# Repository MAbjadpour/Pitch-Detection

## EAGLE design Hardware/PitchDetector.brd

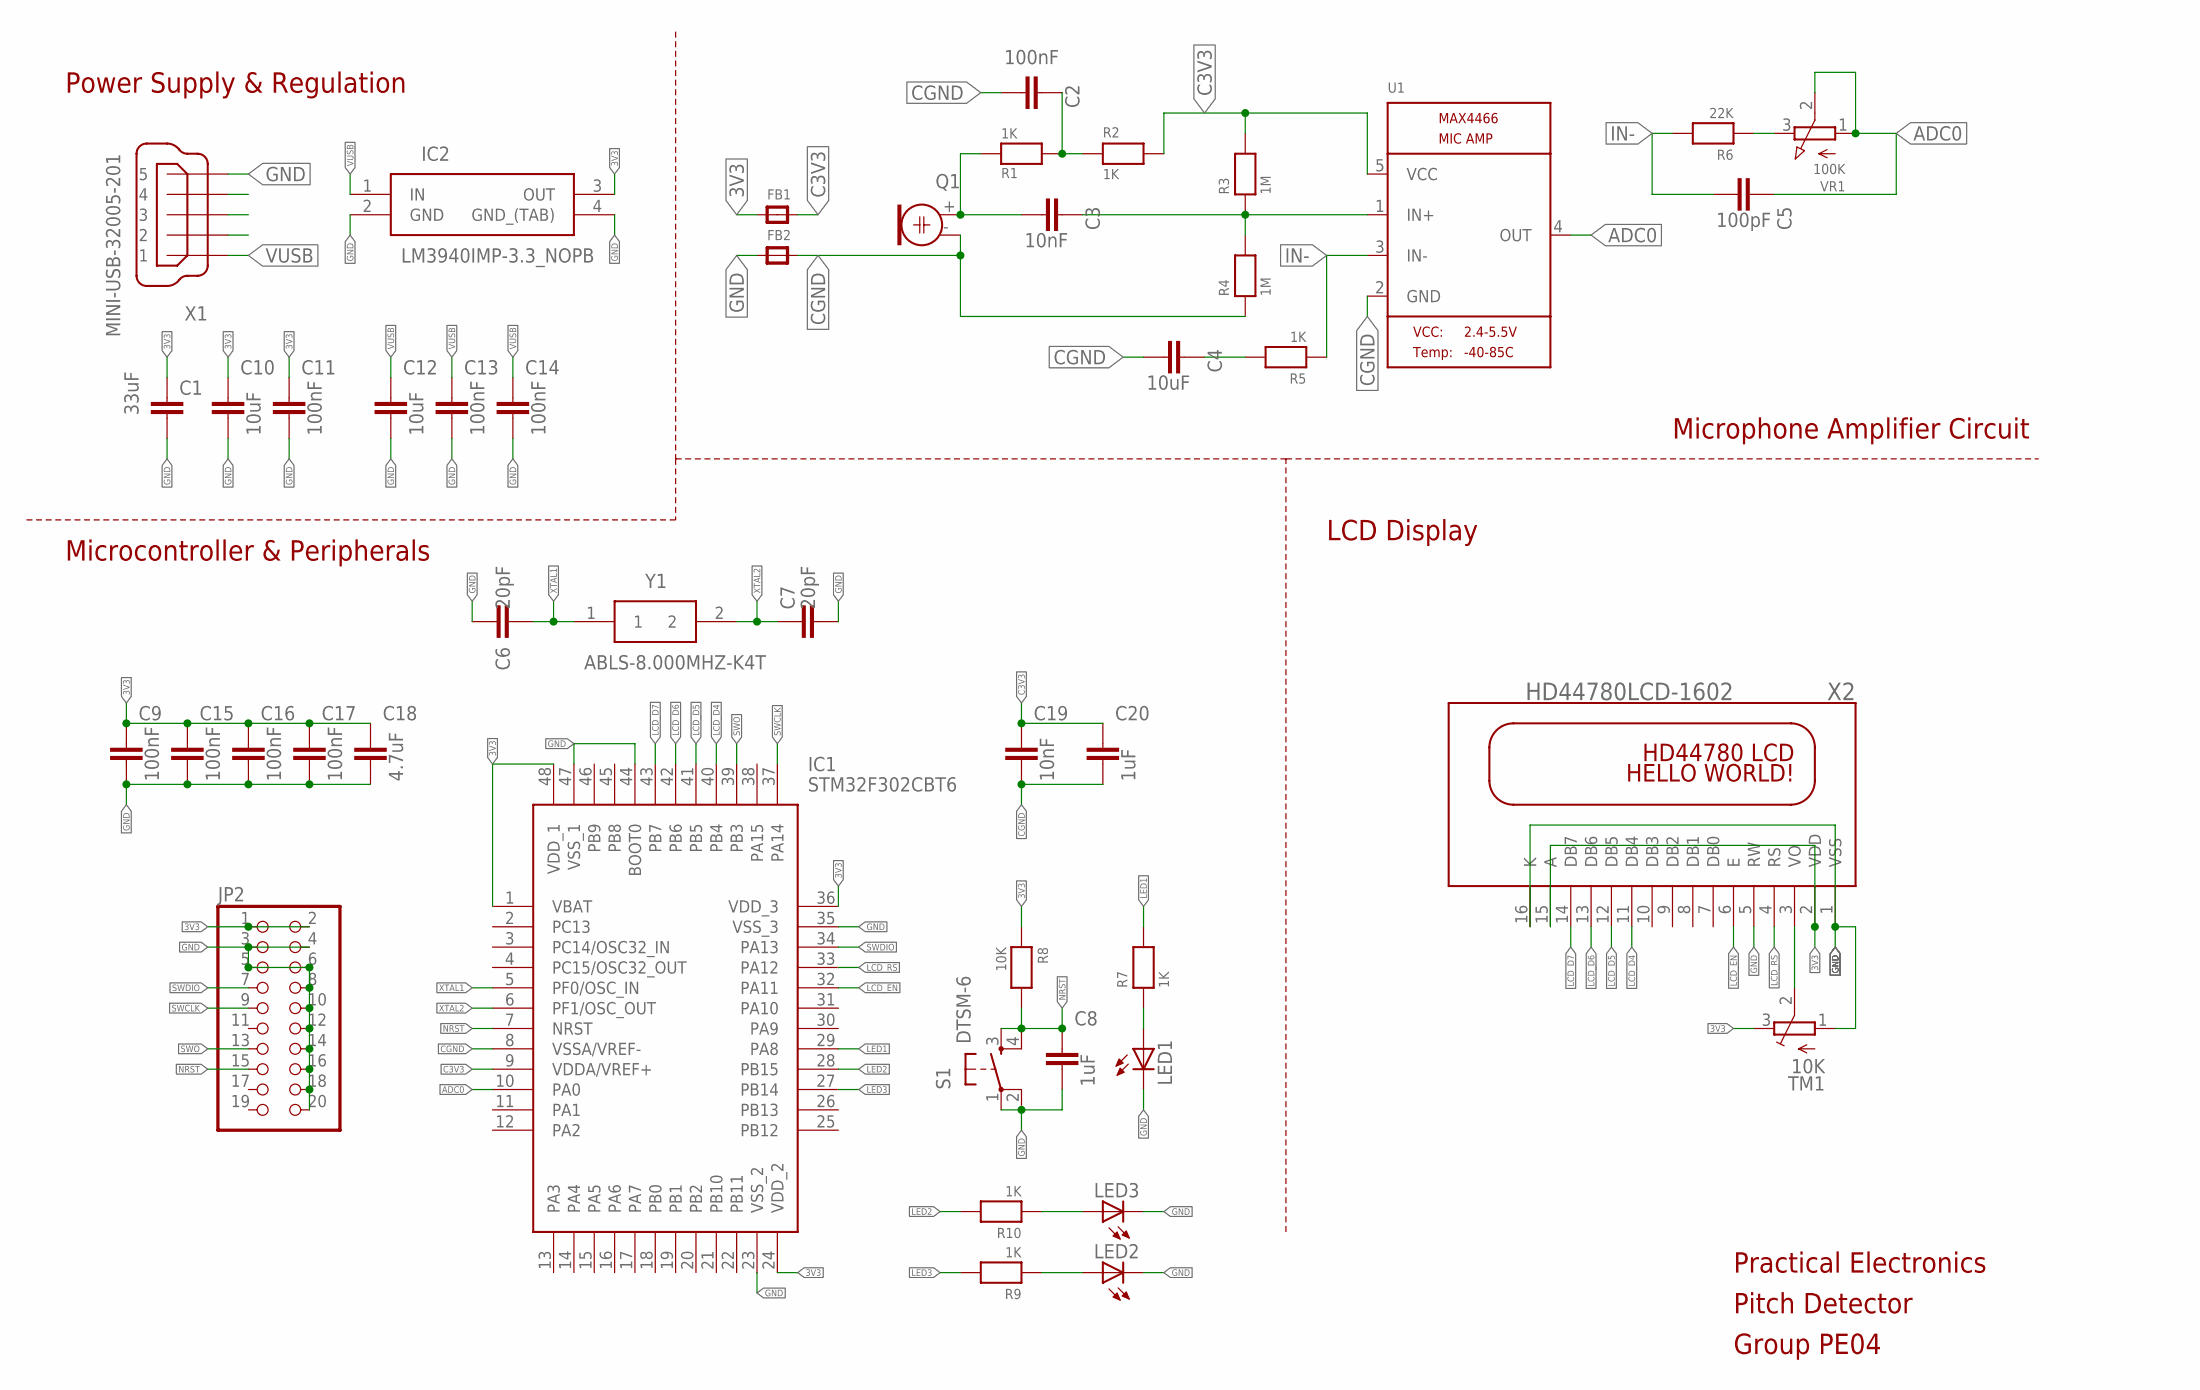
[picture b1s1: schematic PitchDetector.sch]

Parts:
C1: 33uF; C1206K
C2, C9, C11, C13, C14, C15, C16, C17: 100nF; C1206K
C3, C19: 10nF; C1206K
C4, C10, C12: 10uF; C1206K
C5: 100pF; C1206K
C6, C7: 20pF; C0805K
C8, C20: 1uF; C1206K
C18: 4.7uF; C1206K
FB1, FB2: MICROBUILDER_FERRITE_0805; MICROBUILDER__0805
IC1: STM32F302CBT6; QFP50P900X900X160-48N
IC2: LM3940IMP-3.3_NOPB; SOT230P700X180-4N
JP2: PINHD-2X10; 2X10
LED1, LED2, LED3: LEDCHIPLED_1206; CHIPLED_1206
Q1: MICROBUILDER_ELECTRET; MICROBUILDER_ELECTRET_9.7
R1, R2, R5, R7, R9, R10: 1K; MICROBUILDER_1206
R3, R4: 1M; MICROBUILDER_1206
R6: 22K; MICROBUILDER_1206
R8: 10K; MICROBUILDER_1206
S1: DTSM-6
TM1: 10K; TC33X
U1: MICROBUILDER_MAX4466""; MICROBUILDER_SC70-5
VR1: 100K; MICROBUILDER_TRIMPOT_BOURNS_TC33X-2
X1: MINI-USB-32005-201; 32005-201
X2: HD44780LCD-1602; LCD1602
Y1: ABLS-8.000MHZ-K4T; ABLS-12.000MHZ-B2

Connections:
3V3: C1.1, C9.1, C10.1, C11.1, C15.1, C16.1, C17.1, C18.1, FB1.1, IC1.1 (VBAT), IC1.24 (VDD_2), IC1.36 (VDD_3), IC1.48 (VDD_1), IC2.3 (OUT), JP2.1, JP2.2, R8.1, TM1.3 (E), X2.2 (VDD), X2.15 (A)
ADC0: C5.1, IC1.10 (PA0), U1.4 (OUT), VR1.1 (A), VR1.2 (S)
C3V3: C19.1, C20.1, FB1.2, IC1.9 (VDDA/VREF+), R2.2, R3.2, U1.5 (VCC)
CGND: C2.2, C4.2, C19.2, C20.2, FB2.2, IC1.8 (VSSA/VREF-), Q1.- (1), R4.1, U1.2 (GND)
GND: C1.2, C6.1, C7.2, C8.2, C9.2, C10.2, C11.2, C12.2, C13.2, C14.2, C15.2, C16.2, C17.2, C18.2, FB2.1, IC1.23 (VSS_2), IC1.35 (VSS_3), IC1.44 (BOOT0), IC1.47 (VSS_1), IC2.2 (GND), IC2.4 (GND_(TAB)), JP2.3, JP2.4, JP2.5, JP2.6, JP2.8, JP2.10, JP2.12, JP2.14, JP2.16, JP2.18, JP2.20, LED1.C, LED2.C, LED3.C, S1.1, S1.2, TM1.1 (A), X1.5, X2.1 (VSS), X2.5 (RW), X2.16 (K)
IN-: C5.2, R5.1, R6.2, U1.3 (IN-)
LCD_D4: IC1.40 (PB4), X2.11 (DB4)
LCD_D5: IC1.41 (PB5), X2.12 (DB5)
LCD_D6: IC1.42 (PB6), X2.13 (DB6)
LCD_D7: IC1.43 (PB7), X2.14 (DB7)
LCD_EN: IC1.32 (PA11), X2.6 (E)
LCD_RS: IC1.33 (PA12), X2.4 (RS)
LED1: IC1.29 (PA8), R7.2
LED2: IC1.28 (PB15), R10.2
LED3: IC1.27 (PB14), R9.2
unnamed: LED1.A, R7.1
unnamed: C3.2, Q1.+ (2), R1.1
unnamed: C2.1, R1.2, R2.1
unnamed: C3.1, R3.1, R4.2, U1.1 (IN+)
unnamed: R6.1, VR1.3 (E)
unnamed: C4.1, R5.2
unnamed: TM1.2 (S), X2.3 (VO)
unnamed: LED3.A, R10.1
unnamed: LED2.A, R9.1
NRST: C8.1, IC1.7 (NRST), JP2.15, R8.2, S1.3, S1.4
SWCLK: IC1.37 (PA14), JP2.9
SWDIO: IC1.34 (PA13), JP2.7
SWO: IC1.39 (PB3), JP2.13
VUSB: C12.1, C13.1, C14.1, IC2.1 (IN), X1.1
XTAL1: C6.2, IC1.5 (PF0/OSC_IN), Y1.1
XTAL2: C7.1, IC1.6 (PF1/OSC_OUT), Y1.2

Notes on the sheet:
Pitch Detector
Practical Electronics
Group PE04
Microphone Amplifier Circuit
Power Supply & Regulation
LCD Display
Microcontroller & Peripherals

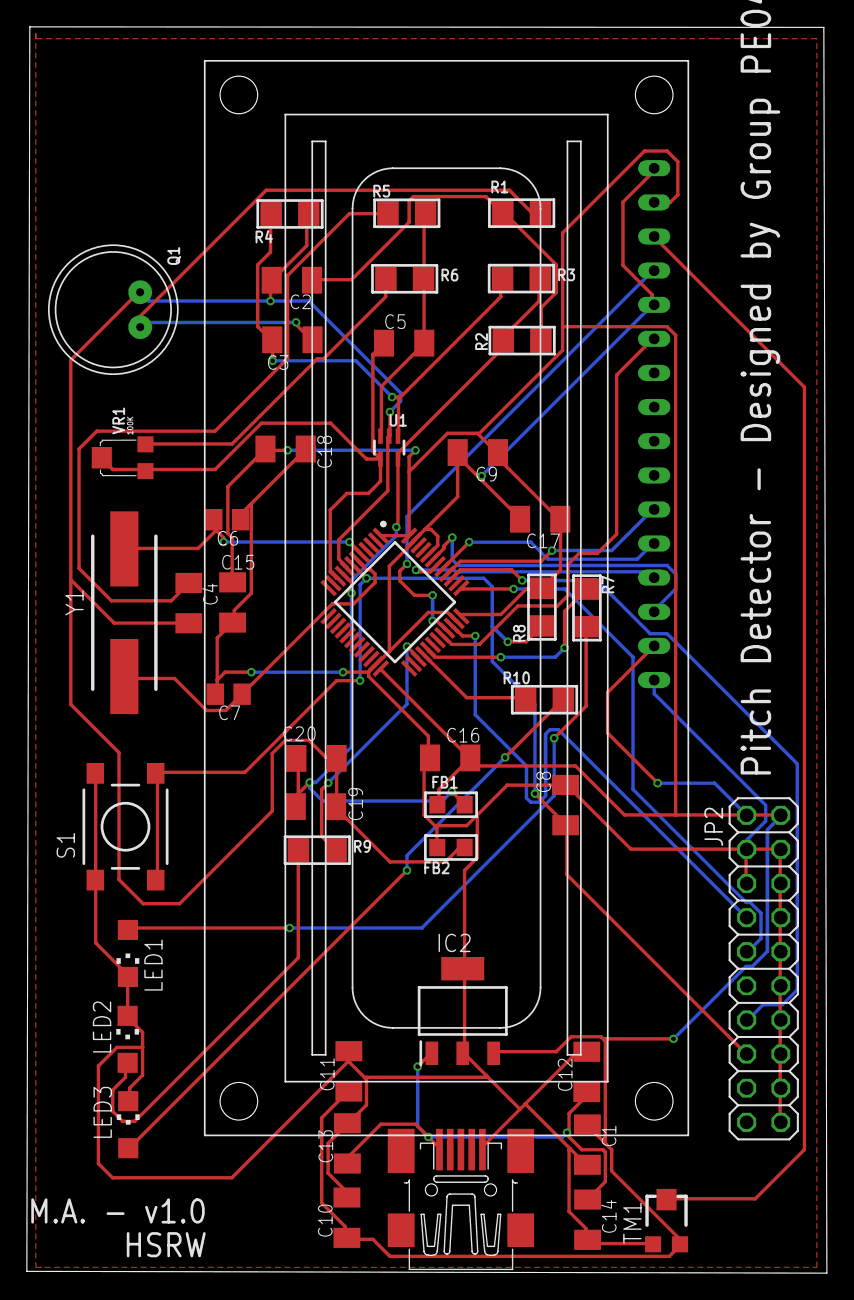
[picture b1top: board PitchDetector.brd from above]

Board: 2 copper layers, 59.6 x 92.8 mm, 46 parts (0 on the bottom side), 31 nets.

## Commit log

2019-11-08 Schematic added.
2019-11-21 Schematic updated.
2019-11-21 PCB added.
2019-11-24 PCB updated.
2019-11-24 Schematic bug fix. PCB updated.
2019-12-01 Stable board and schematic added.
